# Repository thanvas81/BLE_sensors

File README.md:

BLE Sensor PCB – Project Repository

This repository contains all design files, documentation, and supporting materials for my BLE Sensor PCB Thesis.
It includes the hardware schematics, PCB layout, some example firmware, datasheets, and the final report/presentation.

📁 Repository Contents
🔧 BLE_sensors_pcb/

This folder contains the complete PCB design files, including:

Schematic

Board layout

These files represent the final hardware design for the BLE sensor module.

🧠 firmware/

This folder includes the early firmware code used to run the BLE sensor system.

📄 pdf_and_presentation/

This folder contains the final project documentation, including:

Project pdf

Slides / presentation

Thesis or final written report

This is the main reference for understanding the project goals, design, testing, and results.

📚 Datasheets/

Supporting datasheets for components used in the PCB design.

⚙️ .vscode/

Editor and workspace configuration files (for VS Code).

📘 Overview

This project focuses on developing a custom Bluetooth Low Energy sensor board for Indoor Tracking, including hardware design, embedded firmware, and full documentation of the development process.
The PCB, firmware, and final report together demonstrate the complete lifecycle of the system.

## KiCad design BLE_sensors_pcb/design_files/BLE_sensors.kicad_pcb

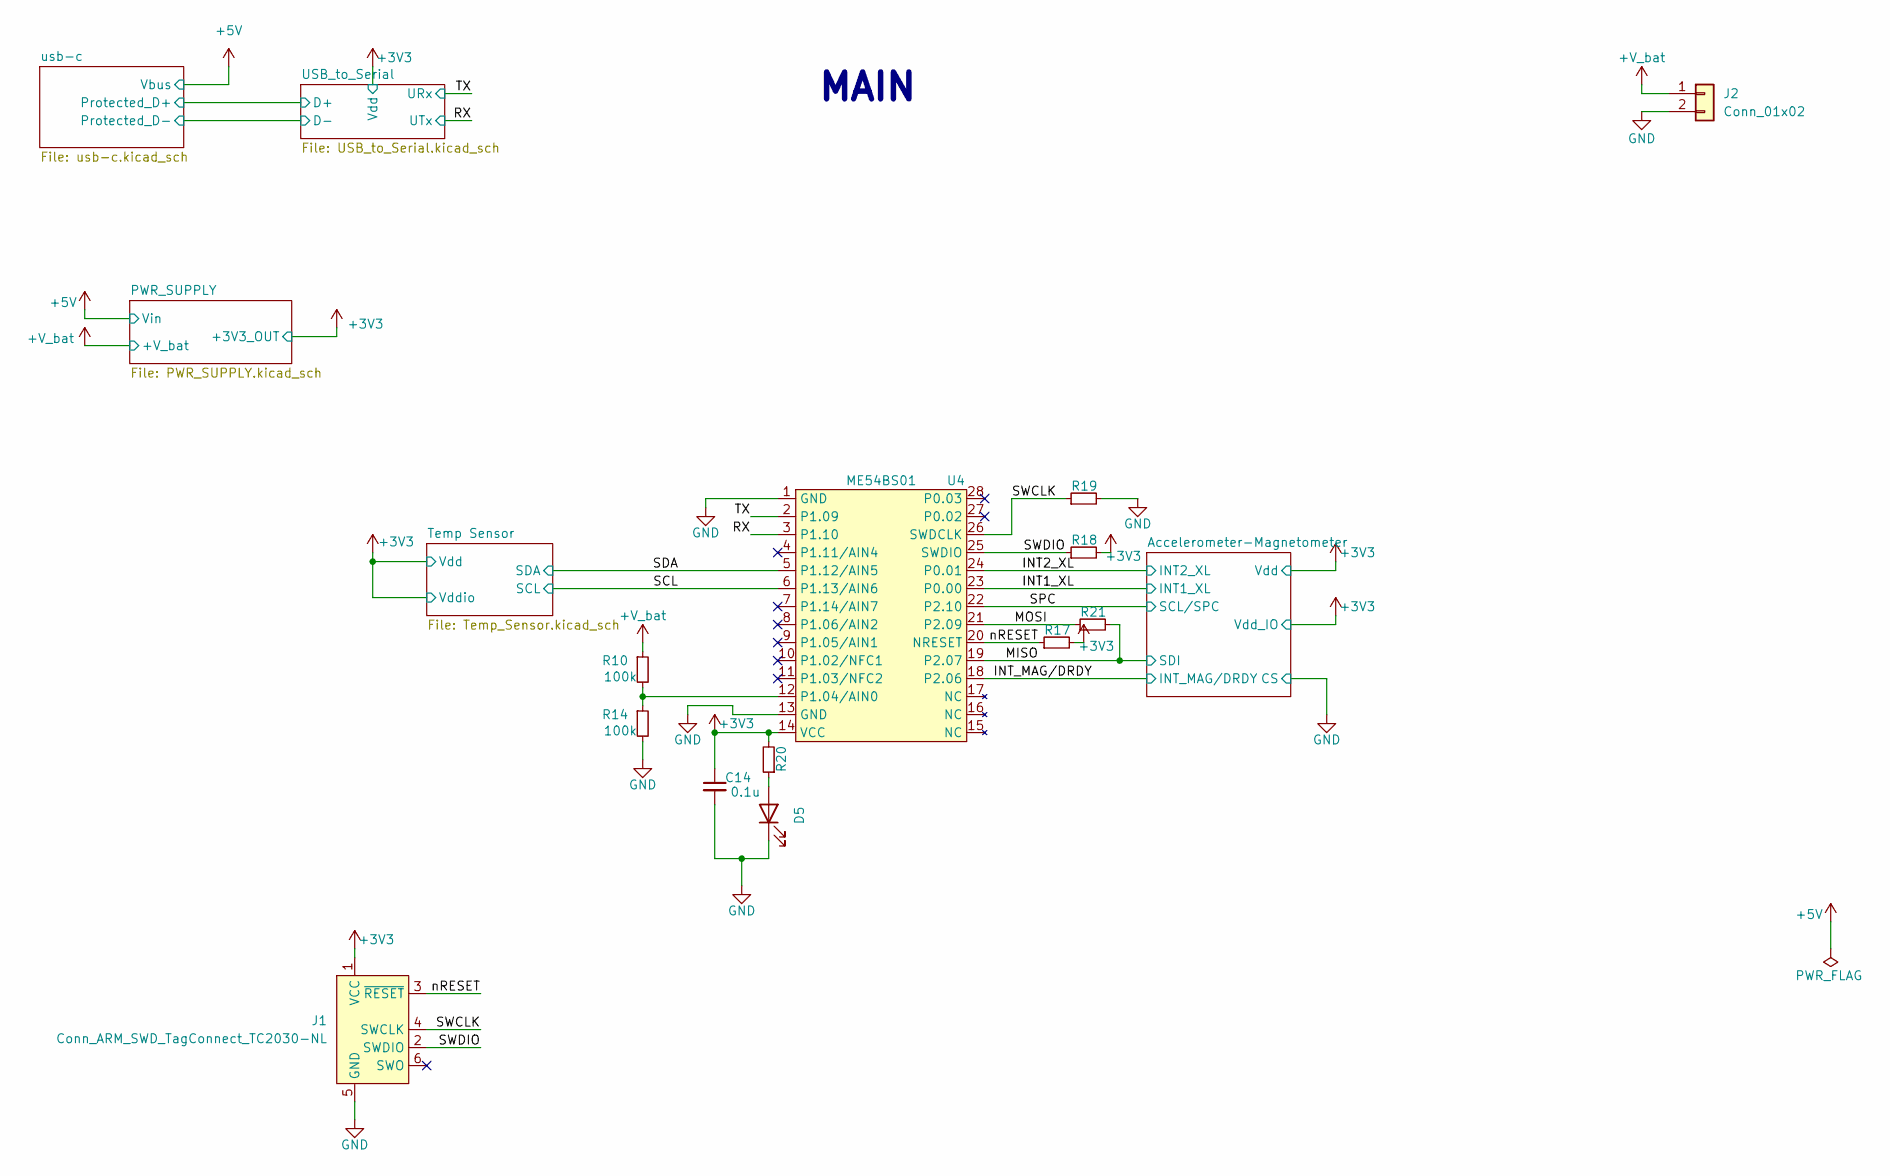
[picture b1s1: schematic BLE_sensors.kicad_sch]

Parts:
C14: 0.1u; C_0603_1608Metric
D5: LED; LED_0603_1608Metric
J1: Conn_ARM_SWD_TagConnect_TC2030-NL; Tag-Connect_TC2030-IDC-NL_2x03_P1.27mm_Vertical
J2: Conn_01x02; PinHeader_1x02_P1.27mm_Vertical
R10, R14: 100k; R_0603_1608Metric
R17, R18, R19, R21: 10k; R_0603_1608Metric
R20: 470R; R_0603_1608Metric
U4: ME54BS01

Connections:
+3V3: C14.1, J1.1 (VCC), R17.2, R18.2, R20.2, U4.14 (VCC); also elsewhere on the board
+V_bat: J2.1, R10.1; also elsewhere on the board
/INT1_XL: U4.23 (P0.00); also elsewhere on the board
/INT2_XL: U4.24 (P0.01); also elsewhere on the board
/INT_MAG/DRDY: U4.18 (P2.06); also elsewhere on the board
/MISO: R21.2, U4.19 (P2.07); also elsewhere on the board
/RX: U4.3 (P1.10); also elsewhere on the board
/SCL: U4.6 (P1.13/AIN6); also elsewhere on the board
/SDA: U4.5 (P1.12/AIN5); also elsewhere on the board
/SPC: U4.22 (P2.10); also elsewhere on the board
/SWCLK: J1.4 (SWCLK), R19.1, U4.26 (SWDCLK)
/SWDIO: J1.2 (SWDIO), R18.1, U4.25 (SWDIO)
/TX: U4.2 (P1.09); also elsewhere on the board
/nRESET: J1.3 (~RESET), R17.1, U4.20 (NRESET)
GND: C14.2, D5.1 (K), J1.5 (GND), J2.2, R14.2, R19.2, U4.1 (GND), U4.13 (GND); also elsewhere on the board
unnamed: D5.2 (A), R20.1
unnamed: R10.2, R14.1, U4.12 (P1.04/AIN0)
unnamed: R21.1, U4.21 (P2.09)

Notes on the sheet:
MAIN

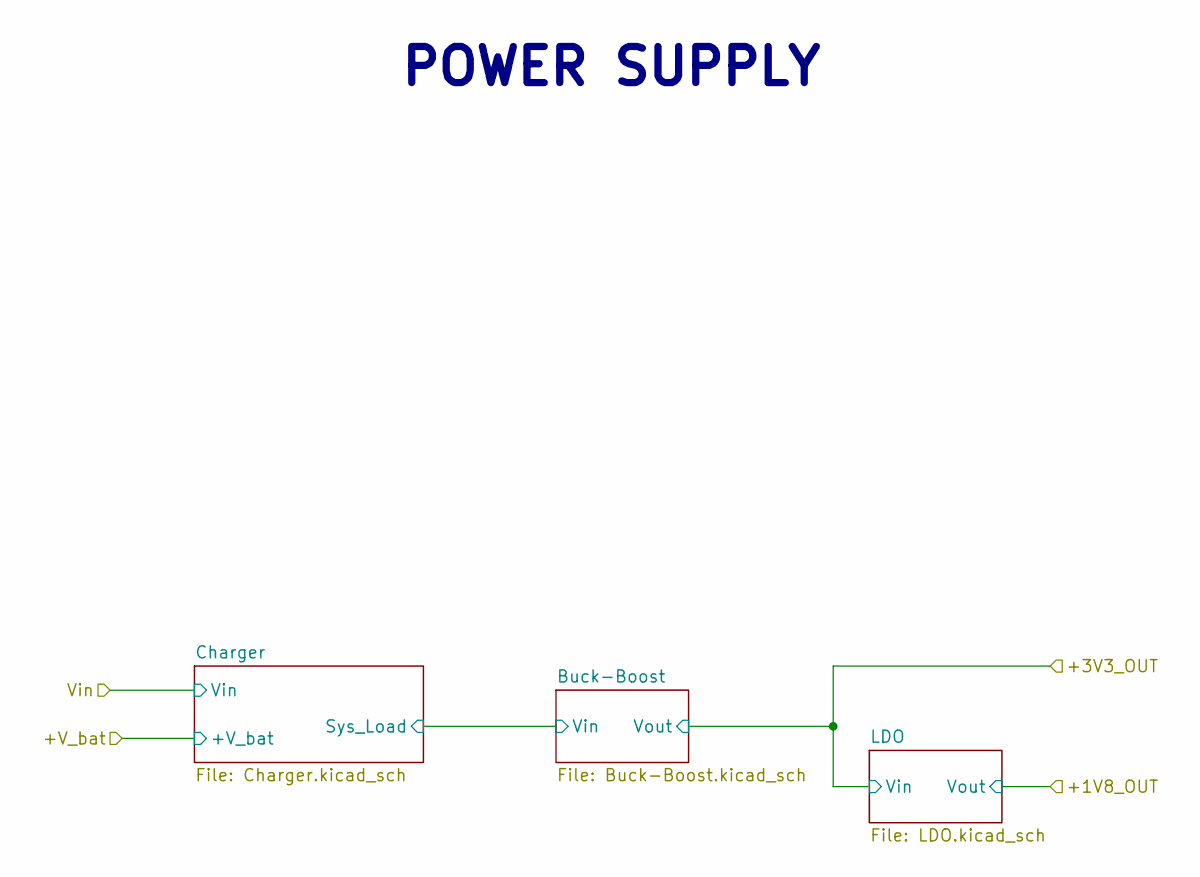
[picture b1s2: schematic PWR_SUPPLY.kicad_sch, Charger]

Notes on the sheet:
POWER SUPPLY

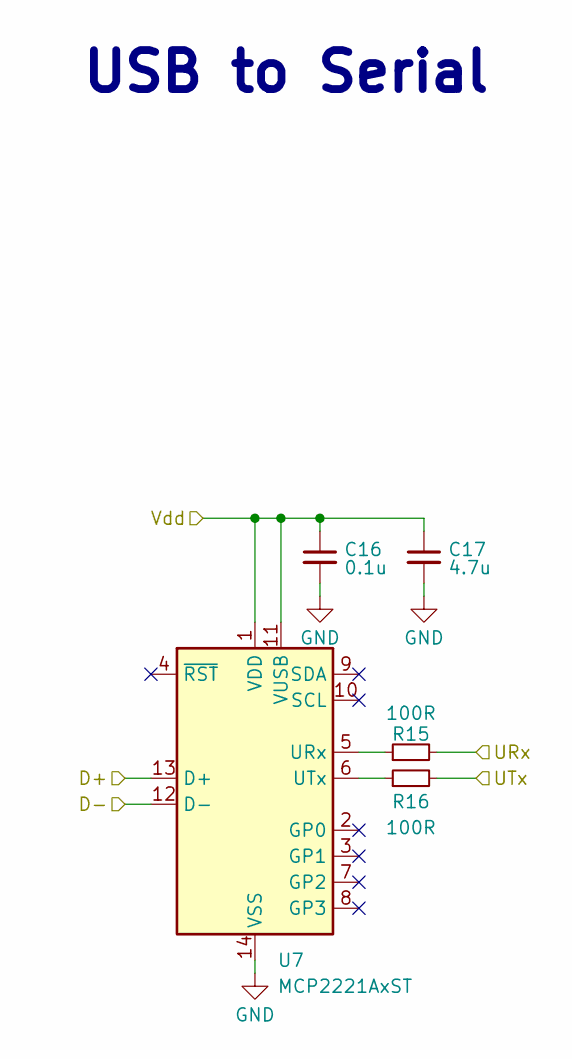
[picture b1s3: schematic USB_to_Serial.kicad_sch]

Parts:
C16: 0.1u; C_0603_1608Metric
C17: 4.7u; C_0805_2012Metric
R15, R16: 100R; R_0603_1608Metric
U7: MCP2221AxST; TSSOP-14_4.4x5mm_P0.65mm

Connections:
+3V3: C16.1, C17.1, U7.1 (VDD), U7.11 (VUSB); also elsewhere on the board
/RX: R16.2; also elsewhere on the board
/TX: R15.2; also elsewhere on the board
GND: C16.2, C17.2, U7.14 (VSS); also elsewhere on the board
unnamed: R15.1, U7.5 (URx)
unnamed: R16.1, U7.6 (UTx)

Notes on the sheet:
USB to Serial

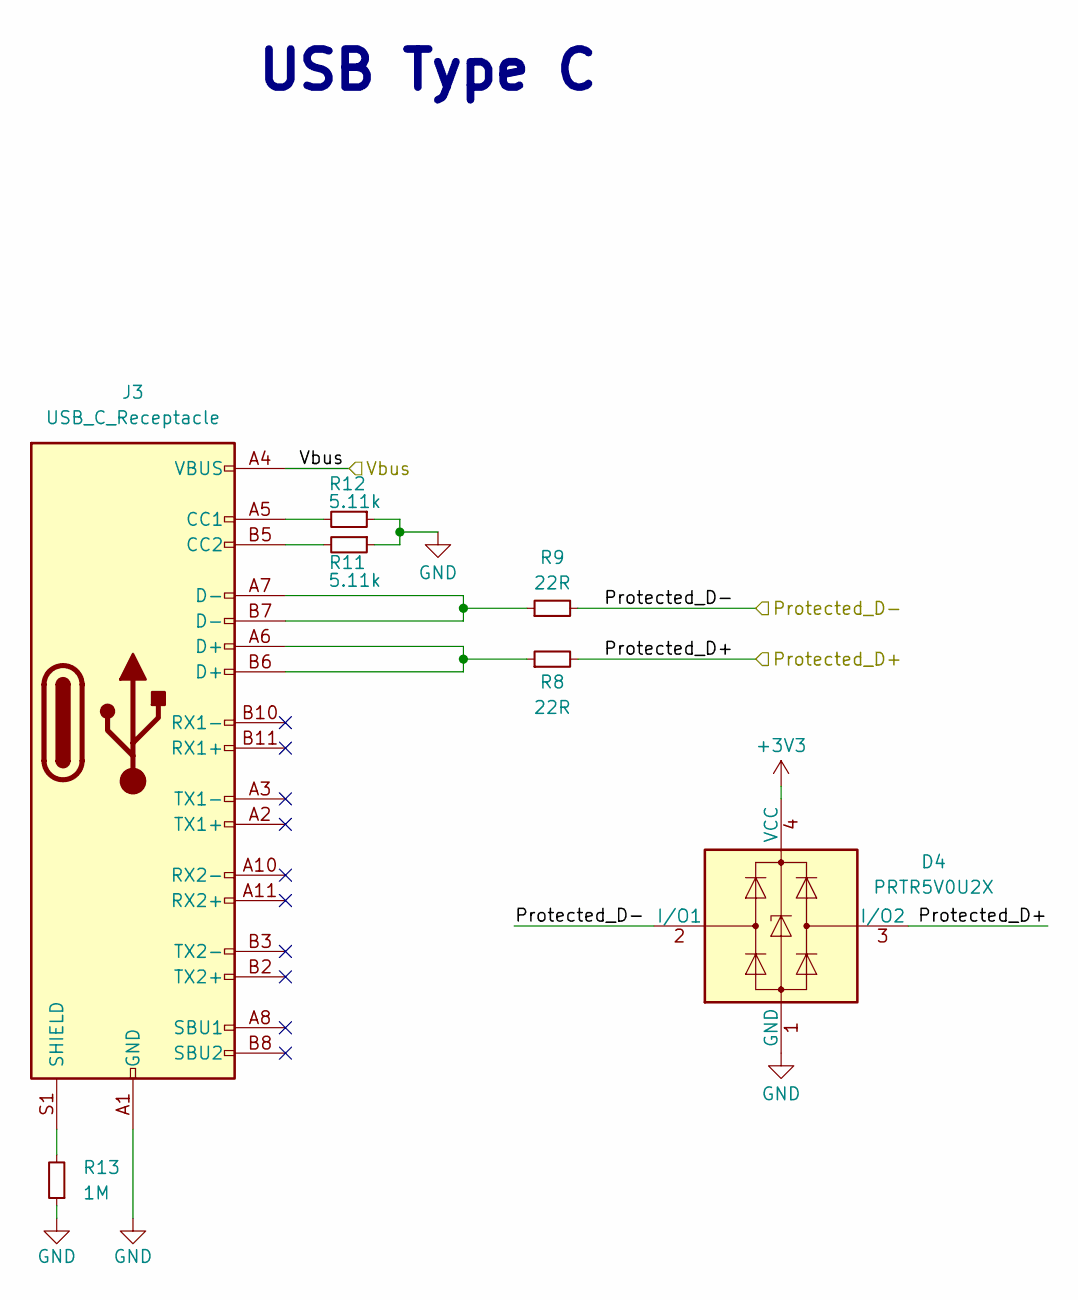
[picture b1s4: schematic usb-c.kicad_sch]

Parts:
D4: PRTR5V0U2X; SOT-143
J3: USB_C_Receptacle; USB_C_Receptacle_G-Switch_GT-USB-7010ASV
R8, R9: 22R; R_0603_1608Metric
R11, R12: 5.11k; R_0603_1608Metric
R13: 1M; R_0603_1608Metric

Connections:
+3V3: D4.4 (VCC); also elsewhere on the board
+5V: J3.A4 (VBUS), J3.A9 (VBUS), J3.B4 (VBUS), J3.B9 (VBUS); also elsewhere on the board
GND: D4.1 (GND), J3.A1 (GND), J3.A12 (GND), J3.B1 (GND), J3.B12 (GND), R11.1, R12.1, R13.1; also elsewhere on the board
unnamed: J3.A5 (CC1), R12.2
unnamed: J3.B5 (CC2), R11.2
unnamed: J3.A6 (D+), J3.B6 (D+), R8.1
unnamed: J3.A7 (D-), J3.B7 (D-), R9.1
unnamed: J3.S1 (SHIELD), R13.2

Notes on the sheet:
USB Type C

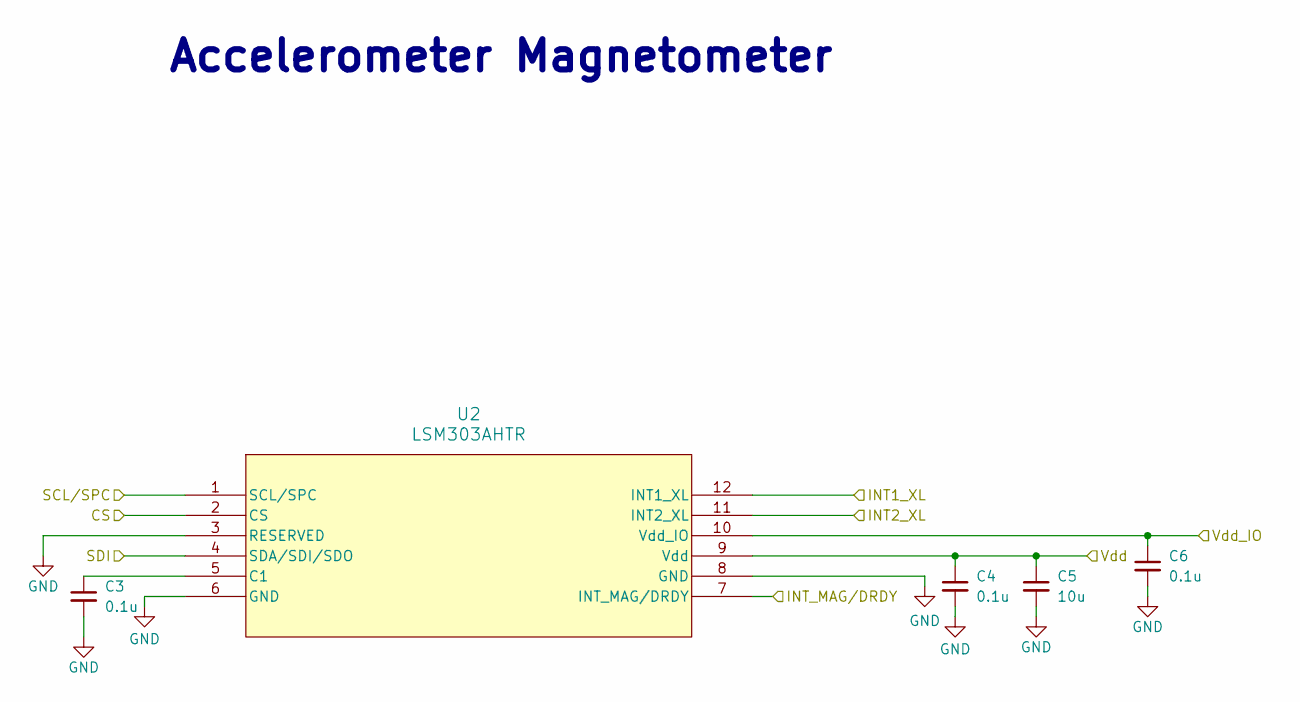
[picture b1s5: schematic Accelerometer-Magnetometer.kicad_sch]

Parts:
C3, C4, C6: 0.1u; C_0603_1608Metric
C5: 10u; C_0805_2012Metric
U2: LSM303AHTR

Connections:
+3V3: C4.1, C5.1, C6.1, U2.9 (Vdd), U2.10 (Vdd_IO); also elsewhere on the board
/INT1_XL: U2.12 (INT1_XL); also elsewhere on the board
/INT2_XL: U2.11 (INT2_XL); also elsewhere on the board
/INT_MAG/DRDY: U2.7 (INT_MAG/DRDY); also elsewhere on the board
/MISO: U2.4 (SDA/SDI/SDO); also elsewhere on the board
/SPC: U2.1 (SCL/SPC); also elsewhere on the board
GND: C3.2, C4.2, C5.2, C6.2, U2.2 (CS), U2.3 (RESERVED), U2.6 (GND), U2.8 (GND); also elsewhere on the board
unnamed: C3.1, U2.5 (C1)

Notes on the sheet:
Accelerometer Magnetometer

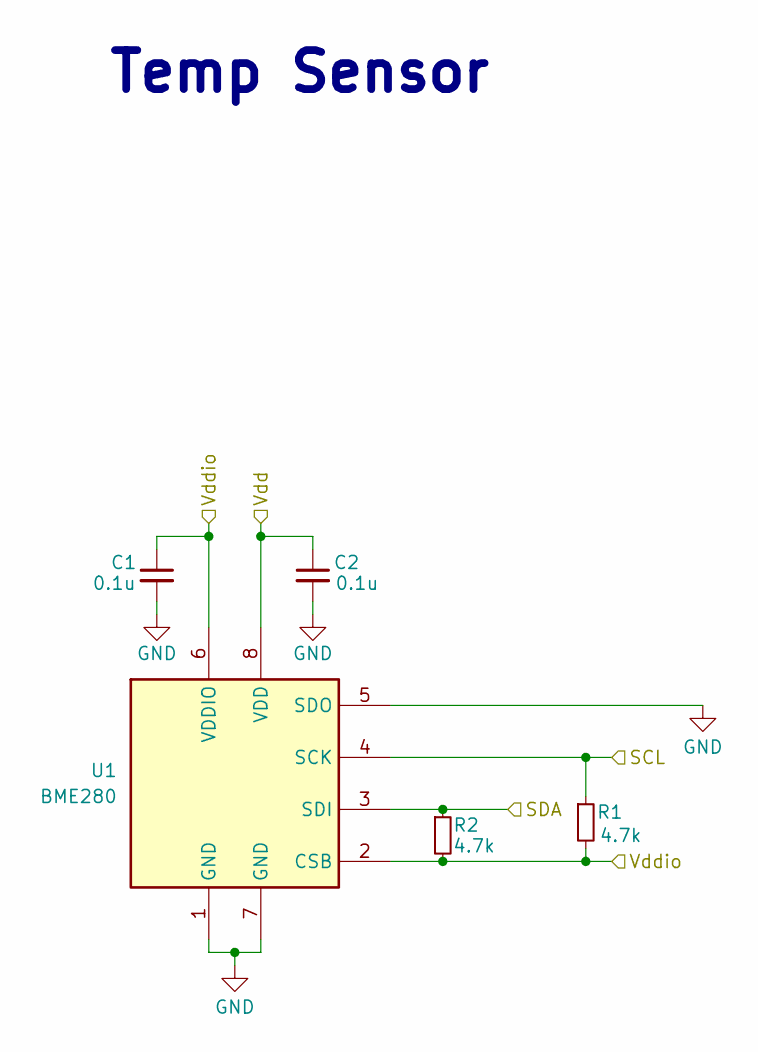
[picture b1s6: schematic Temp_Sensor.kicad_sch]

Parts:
C1, C2: 0.1u; C_0603_1608Metric
R1, R2: 4.7k; R_0603_1608Metric
U1: BME280; Bosch_LGA-8_2.5x2.5mm_P0.65mm_ClockwisePinNumbering

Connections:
+3V3: C1.1, C2.1, R1.2, R2.2, U1.2 (CSB), U1.6 (VDDIO), U1.8 (VDD); also elsewhere on the board
/SCL: R1.1, U1.4 (SCK); also elsewhere on the board
/SDA: R2.1, U1.3 (SDI); also elsewhere on the board
GND: C1.2, C2.2, U1.1 (GND), U1.5 (SDO), U1.7 (GND); also elsewhere on the board

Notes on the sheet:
Temp Sensor

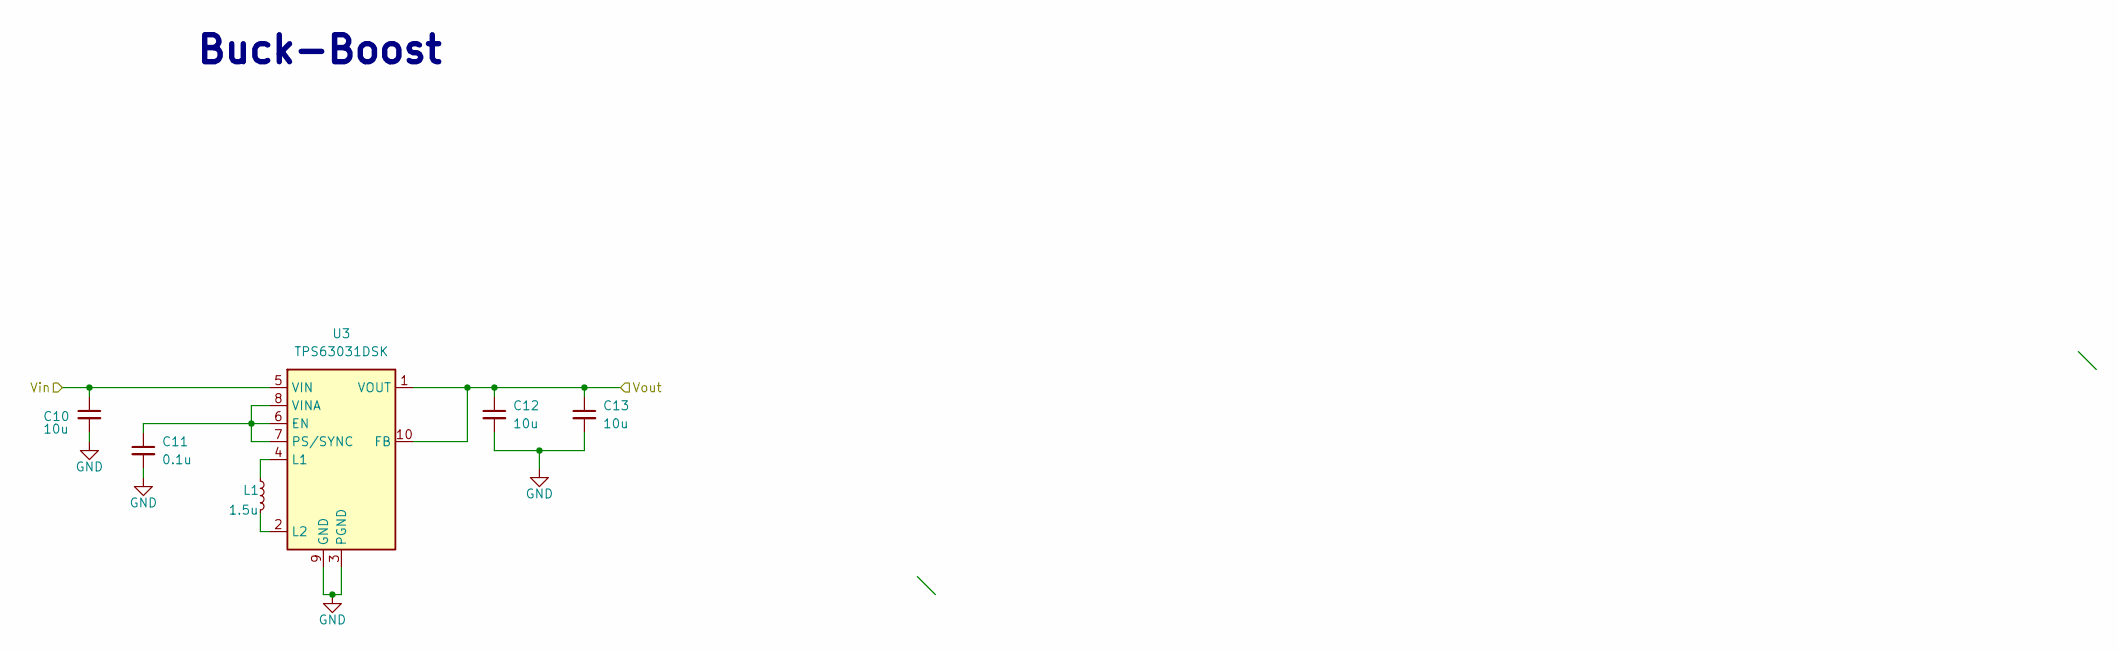
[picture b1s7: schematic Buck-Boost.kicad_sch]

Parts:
C10, C12, C13: 10u; C_0805_2012Metric
C11: 0.1u; C_0603_1608Metric
L1: 1.5u; L_1210_3225Metric
U3: TPS63031DSK; WSON-10-1EP_2.5x2.5mm_P0.5mm_EP1.2x2mm

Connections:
+3V3: C12.1, C13.1, U3.1 (VOUT), U3.10 (FB); also elsewhere on the board
/PWR_SUPPLY/Buck-Boost/Vin: C10.1, U3.5 (VIN); also elsewhere on the board
GND: C10.2, C11.2, C12.2, C13.2, U3.3 (PGND), U3.9 (GND), U3.11 (PGND); also elsewhere on the board
unnamed: C11.1, U3.6 (EN), U3.7 (PS/SYNC), U3.8 (VINA)
unnamed: L1.1, U3.4 (L1)
unnamed: L1.2, U3.2 (L2)

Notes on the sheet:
Buck-Boost

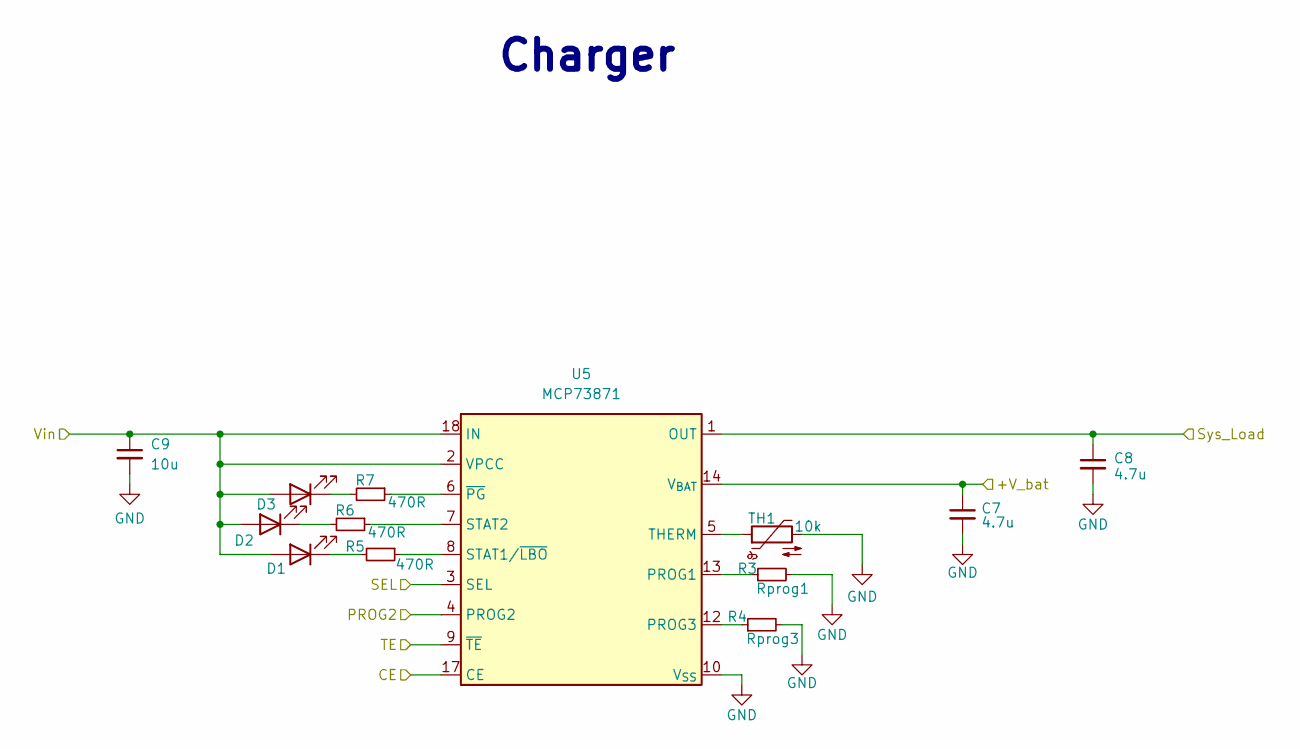
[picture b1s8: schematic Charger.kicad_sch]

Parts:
C7, C8: 4.7u; C_0603_1608Metric
C9: 10u; C_0603_1608Metric
D1, D2, D3: LED; LED_0603_1608Metric
R3: Rprog1; R_0603_1608Metric
R4: Rprog3; R_0603_1608Metric
R5, R6, R7: 470R; R_0603_1608Metric
TH1: 10k; R_0603_1608Metric
U5: MCP73871; QFN-20-1EP_4x4mm_P0.5mm_EP2.5x2.5mm

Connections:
+5V: C9.1, D1.2 (A), D2.2 (A), D3.2 (A), U5.2 (VPCC), U5.4 (PROG2), U5.9 (~TE), U5.17 (CE), U5.18 (IN), U5.19 (IN); also elsewhere on the board
+V_bat: C7.1, U5.14 (V_{BAT}), U5.15 (V_{BAT}), U5.16 (V_{BAT_SENSE}); also elsewhere on the board
/PWR_SUPPLY/Buck-Boost/Vin: C8.1, U5.1 (OUT), U5.20 (OUT); also elsewhere on the board
GND: C7.2, C8.2, C9.2, R3.2, R4.2, TH1.2, U5.3 (SEL), U5.10 (V_{SS}), U5.11 (V_{SS}), U5.21 (V_{SS}); also elsewhere on the board
unnamed: D1.1 (K), R5.2
unnamed: D2.1 (K), R6.2
unnamed: D3.1 (K), R7.2
unnamed: R3.1, U5.13 (PROG1)
unnamed: R4.1, U5.12 (PROG3)
unnamed: R5.1, U5.8 (STAT1/~LBO)
unnamed: R6.1, U5.7 (STAT2)
unnamed: TH1.1, U5.5 (THERM)
unnamed: R7.1, U5.6 (~PG)

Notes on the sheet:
Charger

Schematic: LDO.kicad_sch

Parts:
C14, C15: 1u
U6: TLV70018_SOT23-5; SOT-23-5

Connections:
+3V3: C14.1, U6.1 (IN), U6.3 (EN); also elsewhere on the board
GND: C14.2, C15.2, U6.2 (GND); also elsewhere on the board
unnamed: C15.1, U6.5 (OUT)

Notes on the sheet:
LDO

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
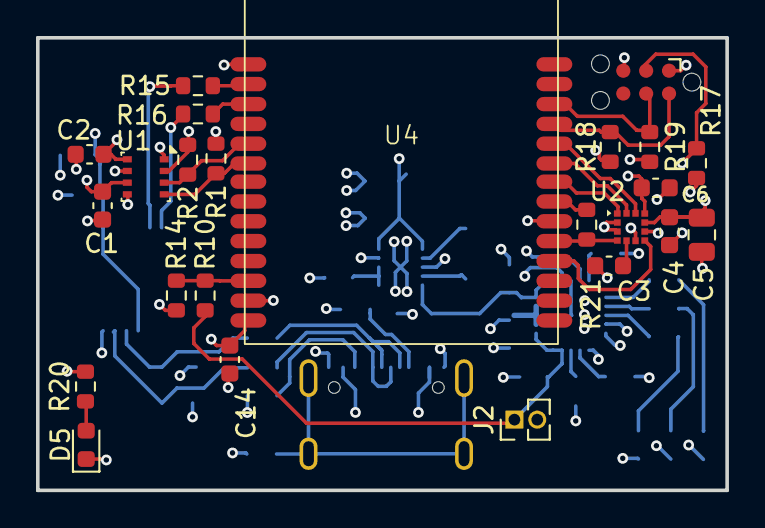
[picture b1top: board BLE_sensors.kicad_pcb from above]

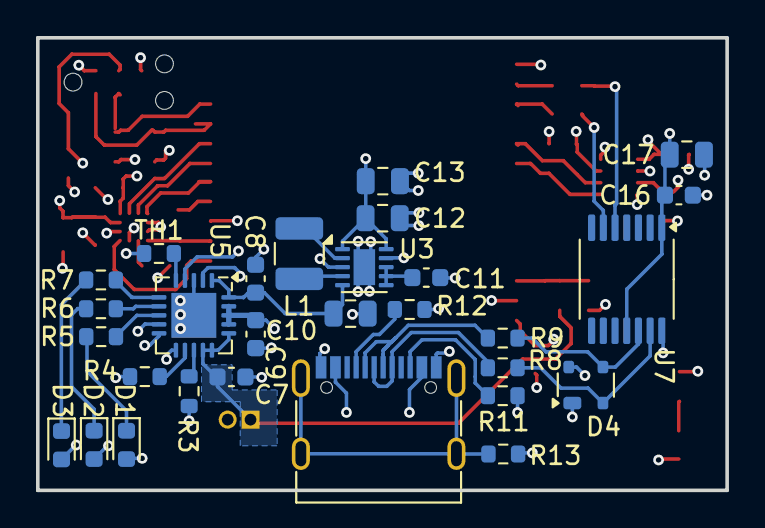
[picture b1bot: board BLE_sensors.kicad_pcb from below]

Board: 4 copper layers, 38.3 x 25.1 mm, 53 parts (29 on the bottom side), 42 nets.

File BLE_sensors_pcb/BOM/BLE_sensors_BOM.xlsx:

Reference | Qty | Value | Footprint | DNP | Ordered | Status
C1, C2, C3, C4, C6, C11, C14, C16 | 8 | 0.1u | Capacitor_SMD:C_0603_1608Metric
C5, C10, C12, C13 | 4 | 10u | Capacitor_SMD:C_0805_2012Metric
C7, C8 | 2 | 4.7u | Capacitor_SMD:C_0603_1608Metric
C9 | 1 | 10u | Capacitor_SMD:C_0603_1608Metric
C17 | 1 | 4.7u | Capacitor_SMD:C_0805_2012Metric
D1, D2, D3 | 3 | LED | LED_SMD:LED_0603_1608Metric
D4 | 1 | PRTR5V0U2X | Package_TO_SOT_SMD:SOT-143
J2 | 1 | Conn_01x02 | Connector_PinHeader_1.27mm:PinHeader_1x02_P1.27mm_Vertical
J3 | 1 | USB_C_Receptacle | Connector_USB:USB_C_Receptacle_G-Switch_GT-USB-7010ASV
L1 | 1 | 1.5u | Inductor_SMD:L_1210_3225Metric
R1, R2 | 2 | 4.7k | Resistor_SMD:R_0603_1608Metric
R3 | 1 | Rprog1 | Resistor_SMD:R_0603_1608Metric
R4 | 1 | Rprog3 | Resistor_SMD:R_0603_1608Metric
R5, R6, R7 | 3 | 470R | Resistor_SMD:R_0603_1608Metric
R8, R9 | 2 | 22R | Resistor_SMD:R_0603_1608Metric
R10, R14 | 2 | 100k | Resistor_SMD:R_0603_1608Metric
R11, R12 | 2 | 5.11k | Resistor_SMD:R_0603_1608Metric
R13 | 1 | 1M | Resistor_SMD:R_0603_1608Metric
R15, R16 | 2 | 100R | Resistor_SMD:R_0603_1608Metric
R17, R18, R19, TH1 | 4 | 10k | Resistor_SMD:R_0603_1608Metric
U1 | 1 | BME280 | Package_LGA:Bosch_LGA-8_2.5x2.5mm_P0.65mm_ClockwisePinNumbering
U2 | 1 | LSM303AHTR | My_Libraries:LSM303AHTR
U3 | 1 | TPS63031DSK | Package_SON:WSON-10-1EP_2.5x2.5mm_P0.5mm_EP1.2x2mm
U4 | 1 | ME54BS01 | My_Libraries:ME54BS01 |  | OK | OK
U5 | 1 | MCP73871 | Package_DFN_QFN:QFN-20-1EP_4x4mm_P0.5mm_EP2.5x2.5mm
U7 | 1 | MCP2221AxST | Package_SO:TSSOP-14_4.4x5mm_P0.65mm

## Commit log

2025-03-09 Added Datasheets
2025-03-09 Added accelerometer datasheet
2025-03-09 Added Data Folder
2025-03-09 Added lsm303ah Datasheet
2025-03-09 Added models for temp sensor and accelerometer
2025-03-09 changes in parts models
2025-03-09 Added lsm303
2025-03-09 added BM15C
2025-04-27 added datashet for me54bs01 and dev board and the me54bs01 to the kicad project
2025-06-01 Refactor schematic and added power supplpy
2025-06-02 Added the usb to serial bridge
2025-06-02 Added schematic
2025-06-03 Footprints and some pcb placement
2025-06-05 Initial pcb placement
2025-06-07 save
2025-06-07 Added layers
2025-06-09 PCB rev1
2025-06-09 Added datasheet
2025-06-10 table
2025-06-10 Changed bme power supply and added pull up to tag connect
2025-06-13 Added a capasitor to me54bs01 pwr supply and added gerbers and schematic
2025-06-14 Added BOM
2025-06-19 changes in BOM orders
2025-06-26 excel change
2025-07-03 fixed spi
2025-07-05 added firmware file
2025-07-06 Working Sending Telemetry
2025-10-17 Added pdf
2025-10-17 added presentation flowchart
2025-10-18 Added presentation draft
2025-10-20 Add flowchart for reflector small flowchart setup and operation
    - Introduced a flowchart diagram in Mermaid syntax to illustrate the setup and operational flow of the reflector system.
    - Included key stages such as initialization, data advertisement loop, channel sounding, and power management.
    - Enhanced clarity on the system's behavior during motion detection and sleep states.
2025-10-21 presentation
2025-10-21 Add Thesis presentation file
2025-10-21 Presentation Update
2025-10-21 Update pp
2025-10-21 added presentation text
2025-10-22 presentation speach
2025-10-23 Final speatch and small thesis change
2025-10-23 Final
2025-11-30 Add README for BLE Sensor PCB project
    This README provides an overview of the BLE Sensor PCB project, including its contents and purpose.
2026-06-26 test
2026-06-26 test2
